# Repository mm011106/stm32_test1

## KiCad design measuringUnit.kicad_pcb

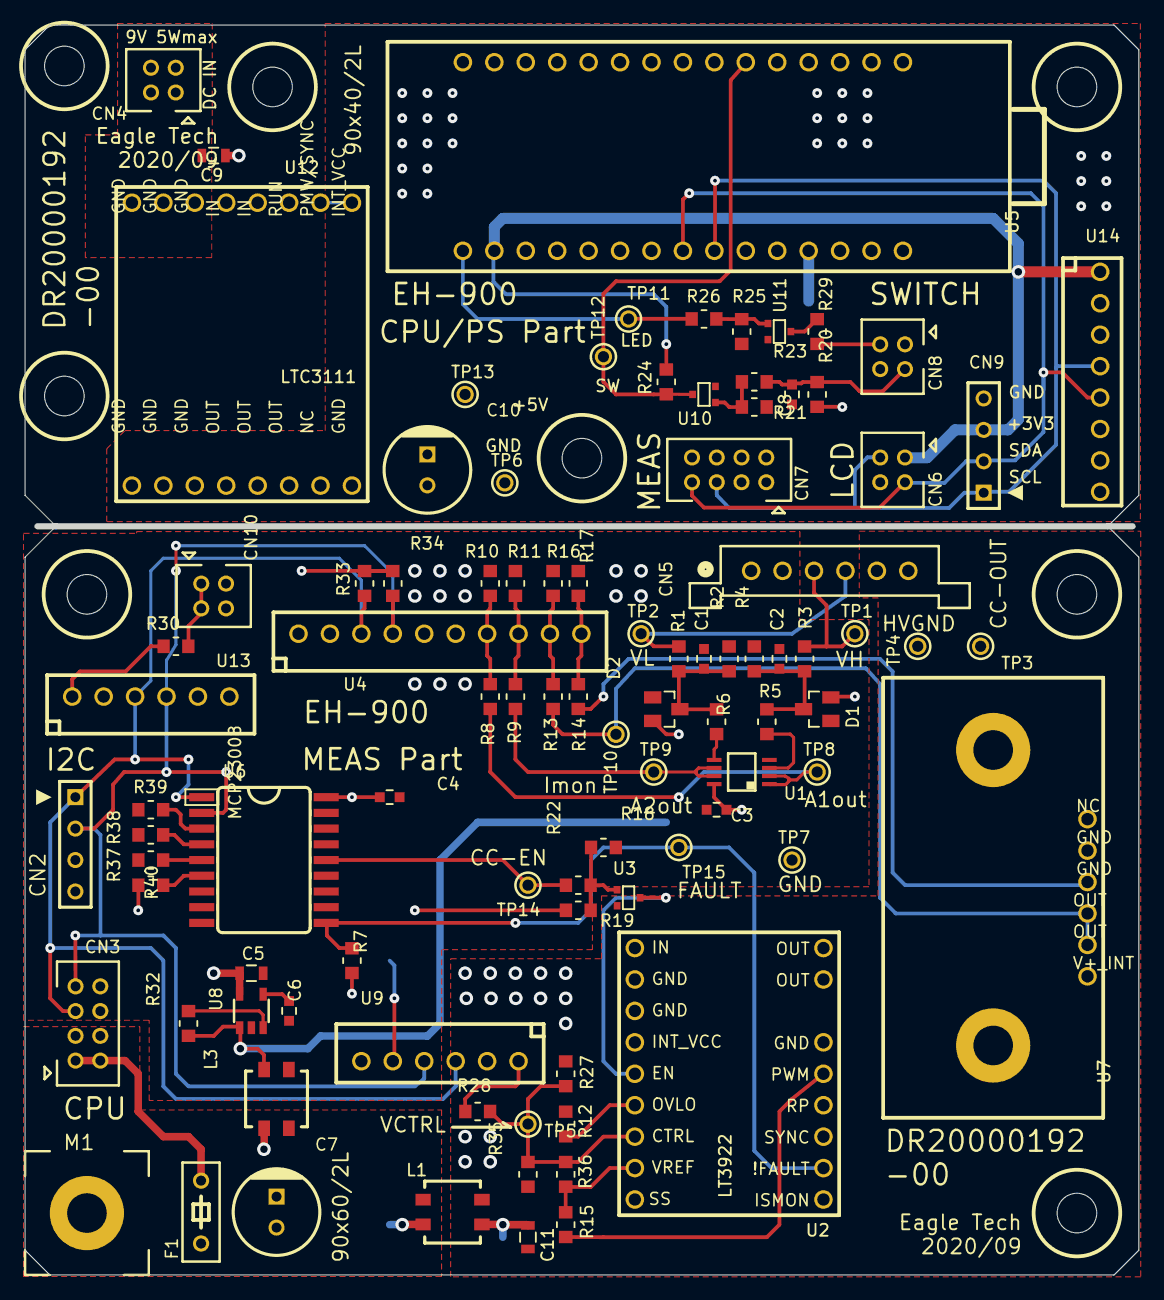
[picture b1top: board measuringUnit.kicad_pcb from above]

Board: 2 copper layers, 89.6 x 100.6 mm, 102 parts (0 on the bottom side), 59 nets.

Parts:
@HOLE0, @HOLE1, @HOLE2, @HOLE3, @HOLE4, @HOLE5, @HOLE6, @HOLE7: (no value)
C1, C2, C3, C4, C8: 0.1u/50V; CM1608
C5: 4.7u/25V; CM2012
C6: 10n; CM1608
C7, C10: 56u/10V/OS; PHI_6.3
C9, C11: 10u/25V; CM2012
CN2, CN9: 826646-4; PIN_HEADER_4PIN
CN3, CN7: DF11-8DP-2DSA
CN4, CN6, CN8, CN10: DF11-4DP-2DSA
CN5: HNC2_6DS
D1, D2: 1SS; SOT23
F1: RXEF; 8X3_5.08
L1, L3: ACM4520
M1: VAB-3-10; VAB_3_10_CONTACT
R1, R3: 910k; RM1608
R2, R4, R28: 100k; RM1608
R5, R6, R22, R23, R26: 1k/THICK; RM1608
R7, R19, R24, R32, R33, R34, R37, R38, R39, R40: 100k/THICK; RM1608
R8, R9: 6.2k; RM1608
R10, R11: 4.3k; RM1608
R12, R15: 0; RM1608
R13, R14, R30: 100/THICK; RM1608
R16, R17, R18: ---; RM1608
R20: 4.7k/THICK; RM1608
R21: 15k/THICK; RM1608
R25: 200k/THICK; RM1608
R27: 33k; RM1608
R29: 330/THICK; RM1608
R35: 2.4k; RM1608
R36: 7.5k; RM1608
TP1, TP2, TP3, TP4, TP5, TP6, TP7, TP8, TP9, TP10, TP11, TP12, TP13, TP14, TP15: TP-LC3G; TP_TH_0R9MM
U1: OPA2344EA; MSO8_AEL
U2: LT3922
U3, U10, U11: SSM3K15AFU; SC-70
U4: ADAFURUIT_ADS115; SIP_10PIN
U5: NUCLEO-32_F303K8; NUCLEO_32
U6: MCP23008; SO18_400MIL
U7: LTC6102
U8: TPS799DDC; SOT-23-5
U9, U13: SPARKFUN_MCP4725; SIP_6PIN
U12: LTC3111
U14: ADAFRUIT_FRAM_I2C; SIP_8PIN

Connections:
/measuringUnit_1/OE: U2.5, U3.3
/measuringUnit_1/SCL: CN2.1, CN3.5, R33.1, U4.3, U6.1, U9.3, U13.3
/measuringUnit_1/SDA: CN2.2, CN3.7, R34.1, U4.4, U6.2, U9.4, U13.4
/measuringUnit_1/VCC+: C7.POS, F1.1, L1.4, L3.3
/measuringUnit_1/VCC-: C7.NEG, CN3.3, CN3.4, L1.3, L3.4
/measuringUnit_1/VREF: R15.2, R36.1, U2.8
/measuringUnit_1/~IOUT_EN: R22.2, TP14.1, U6.14
/measuringUnit_2/+3V3: CN6.1, CN9.3, R24.2, U14.1
/measuringUnit_2/CPU_SCL: CN6.2, CN7.5, CN9.1, U5.4-7, U14.4
/measuringUnit_2/CPU_SDA: CN6.3, CN7.7, CN9.2, U5.4-8, U14.5
/measuringUnit_2/LED_DRIVE: CN8.2, R29.2
/measuringUnit_2/PB0: R24.1, TP12.1, U5.3-6, U10.3
/measuringUnit_2/PB3: R26.1, TP11.1, U5.4-15
/measuringUnit_2/R+5V: C10.POS, CN7.1, CN7.2, CN8.1, R20.2, TP13.1, U12.12, U12.13, U12.14
/measuringUnit_2/SW_IN: C8.1, CN8.3, R20.1, R23.1
AGND: C1.2, C2.2, C3.2, C4.1, C5.2, C6.2, CN2.4, CN3.6, CN3.8, CN5.1, CN5.2, CN10.3, CN10.4, D1.1, D2.1, L3.1, M1.CASE1, R2.1, R4.1, R10.1, R11.1, R16.1, R17.1, R18.1, R37.1, R38.1, R39.1, TP7.1, U1.4, U4.2, U6.9, U8.2, U9.6, U13.2, U13.6
DGND: C8.2, C10.NEG, CN6.4, CN7.3, CN7.4, CN7.6, CN7.8, CN8.4, CN9.4, R21.1, R25.1, TP6.1, U10.2, U11.2, U12.9, U12.10, U12.11, U12.16, U14.2, U14.3, U14.6, U14.7, U14.8
GND: U5.3-4, U5.4-2
HVGND: C11.2, CN5.6, L1.2, R12.2, R14.1, R27.2, R35.2, TP4.1, U2.2, U2.3, U2.15, U3.2, U7.4, U7.5, U9.2
unnamed: C1.1, D2.3, R1.1, R2.2, R6.1
unnamed: C2.1, D1.3, R3.1, R4.2, R5.1
unnamed: C6.1, U8.4
unnamed: C9.1, CN4.1, CN4.2, U12.3, U12.4, U12.5
unnamed: C9.2, CN4.3, CN4.4, U12.6, U12.7, U12.8
unnamed: C11.1, L1.1, U2.1
unnamed: CN3.1, CN3.2, F1.2
unnamed: CN5.3, R3.2, TP1.1
unnamed: CN5.4, R1.2, TP2.1
unnamed: CN5.5, TP3.1, U7.LOAD
unnamed: CN10.1, CN10.2, R30.2
unnamed: R5.2, U1.3
unnamed: R6.2, U1.5
unnamed: R7.1, TP15.1, U2.11, U6.10
unnamed: R8.1, TP8.1, U1.1, U1.2
unnamed: R9.1, TP9.1, U1.6, U1.7
unnamed: R8.2, R10.2, U4.7
unnamed: R9.2, R11.2, U4.8
unnamed: R12.1, U2.6
unnamed: R13.1, TP10.1, U7.2, U7.3
unnamed: R13.2, R16.2, U4.9
unnamed: R14.2, R17.2, U4.10
unnamed: R15.1, U2.14
unnamed: R18.2, R19.1, R22.1, U3.1
unnamed: R21.2, R23.2, U10.1
unnamed: R25.2, R26.2, U11.1
unnamed: R27.1, R28.1, R35.1, R36.2, TP5.1, U2.7
unnamed: R28.2, U9.1
unnamed: R29.1, U11.3
unnamed: R30.1, U13.1
unnamed: R32.1, U8.3
unnamed: R37.2, U6.5
unnamed: R38.2, U6.4
unnamed: R39.2, U6.3
unnamed: R40.1, U6.6
unnamed: U2.17, U2.18, U7.1, U7.V+
unnamed: U5.3-3, U5.4-3
unnamed: U12.1, U12.2
VA+5: C3.1, D1.2, D2.2, L3.2, R32.2, U1.8, U8.1
VD+3V3: C4.2, C5.1, R7.2, R19.2, R33.2, R34.2, R40.2, U4.1, U6.18, U8.5, U9.5, U13.5

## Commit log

2021-11-04 commit 1 :add new text
2021-11-04 commit2 : add lines 3,4
2021-11-04 commit3 branch1
2021-11-04 commit 3 :main add lines
2021-11-04 no way!
2021-11-04 Delete history.txt
    tried rebase command on this file.
2021-11-29 UPDATE 1-1
2022-04-07 test update
